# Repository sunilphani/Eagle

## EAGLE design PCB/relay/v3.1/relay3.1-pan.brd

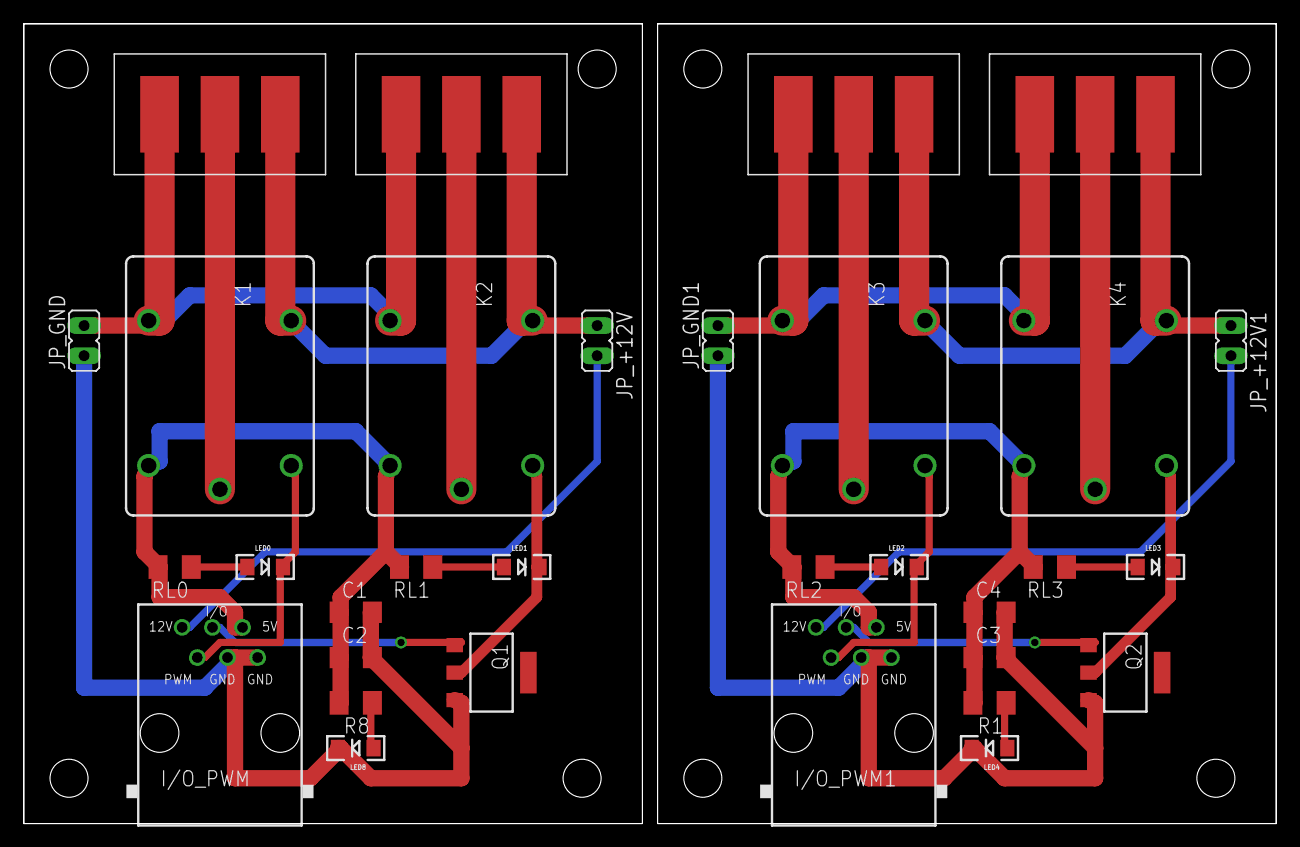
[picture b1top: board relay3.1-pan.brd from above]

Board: 2 copper layers, 105.4 x 67.3 mm, 32 parts (0 on the bottom side), 26 nets.

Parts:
C1, C4: 10uF; C1206
C2, C3: 100nF; C1206
I/O_PWM, I/O_PWM1: I2C 1; RJ12-STRAIGHT
JP_+12V, JP_+12V1: JP1
JP_GND, JP_GND1: JP1
K1, K2, K3, K4: JS-M1-9V-5; JS-M
LED0, LED1, LED2, LED3, LED4, LED8: LED-1206
Q1, Q2: BSP75; PG-SOT-223
R1, R8: 1K; M1206
RL0, RL1, RL2, RL3: 1K; M1206
X1, X2, X3, X4: 22-23-20315.08S; 3-PIN-5.08S

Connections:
+5V: C1.1, C2.1, I/O_PWM.+5V, K1.2, K2.2, R8.2, RL0.2, RL1.2
+5V1: C3.1, C4.1, I/O_PWM1.+5V, K3.2, K4.2, R1.2, RL2.2, RL3.2
+12V: I/O_PWM.+12V, JP_+12V.2
+12V1: I/O_PWM1.+12V, JP_+12V1.2
+12VRELAY: JP_+12V.1, K1.NO, K2.NO, X1.1, X2.1
+12VRELAY1: JP_+12V1.1, K3.NO, K4.NO, X3.1, X4.1
GND: C1.2, C2.2, I/O_PWM.GND1, I/O_PWM.GND2, JP_GND.1, LED8.C, Q1.3
GND1: C3.2, C4.2, I/O_PWM1.GND1, I/O_PWM1.GND2, JP_GND1.1, LED4.C, Q2.3
GNDRELAY: JP_GND.2, K1.NC, K2.NC, X1.3, X2.3
GNDRELAY1: JP_GND1.2, K3.NC, K4.NC, X3.3, X4.3
I/O: I/O_PWM.I/O, Q1.1
I/O1: I/O_PWM1.I/O, Q2.1
unnamed: K2.1, LED1.C, Q1.2
unnamed: LED0.A, RL0.1
unnamed: K4.1, LED3.C, Q2.2
unnamed: LED1.A, RL1.1
unnamed: K2.C, X1.2
unnamed: LED2.A, RL2.1
unnamed: LED3.A, RL3.1
unnamed: LED4.A, R1.1
unnamed: K4.C, X3.2
unnamed: LED8.A, R8.1
POWER1: K1.C, X2.2
POWER2: K3.C, X4.2
PWM: I/O_PWM.PWM, K1.1, LED0.C
PWM1: I/O_PWM1.PWM, K3.1, LED2.C

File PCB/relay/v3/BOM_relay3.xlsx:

Qty | Value | Device | Package | Parts | Description
2 |  | JP1Q | JP1 | JP_+12V
3 |  | LED1206 | LED-1206 | LED0
1 | 100nF | C-EUC1206 | C1206 | C2 | CAPACITOR
1 | 10uF | C-EUC1206 | C1206 | C1 | CAPACITOR
3 | 1K | R-EU_M1206 | M1206 | R8
2 | 22-23-20315.08S | 22-23-20315.08S | 3-PIN-5.08S | X1
1 | BSP75 | BSP613P | PG-SOT-223 | Q1 | SIPMOS (R) Small-Signal-Transistor P-Channel (2 Drain)
1 | I2C 1 | RJ12STRAIGHT | RJ12-STRAIGHT | I/O_PWM | CORCOM Modular RJ Jacks No Shield
2 | JS-M1-9V-5 | JS-M1-9V-5 | JS-M | K1

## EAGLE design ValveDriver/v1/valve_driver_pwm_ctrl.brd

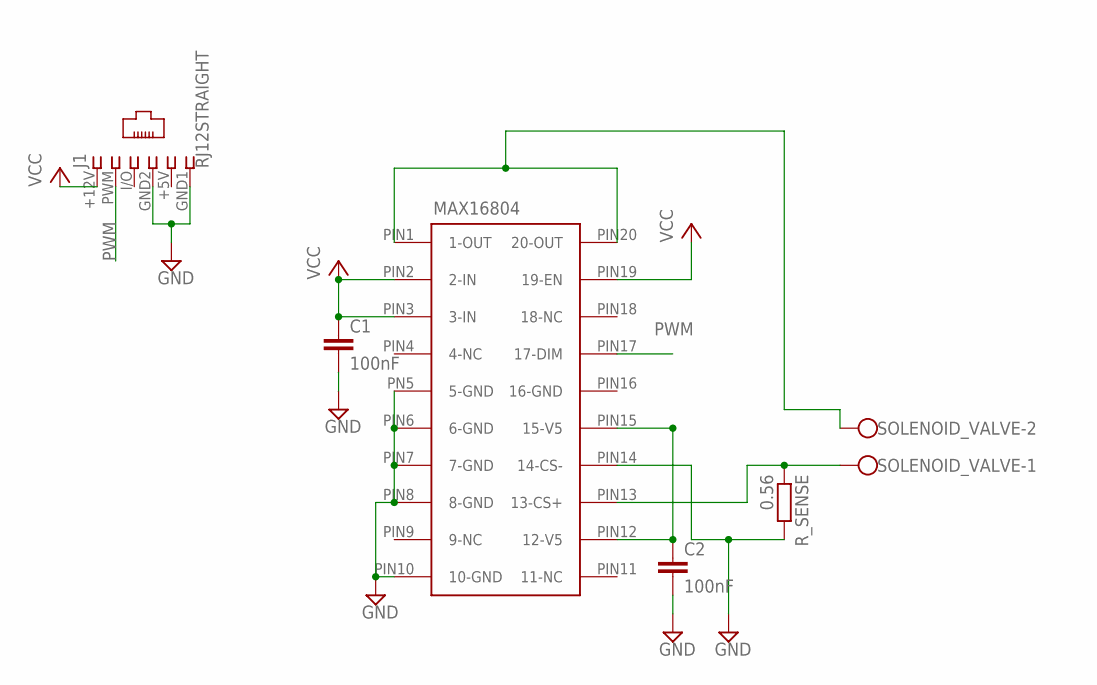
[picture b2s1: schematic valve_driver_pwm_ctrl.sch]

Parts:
C1, C2: 100nF; C1206
J1: RJ12STRAIGHT; RJ12-STRAIGHT
R_SENSE: 0.56; M1206
SOLENOID_VALVE: W237-102
U$1: MAX16804ATP+; TQFN-20

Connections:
GND: C1.2, C2.2, J1.GND1 (6), J1.GND2 (4), R_SENSE.2, U$1.PIN6 (6-GND), U$1.PIN7 (7-GND), U$1.PIN8 (8-GND), U$1.PIN10 (10-GND), U$1.PIN14 (14-CS-), U$1.PN5 (5-GND)
unnamed: SOLENOID_VALVE.2, U$1.PIN1 (1-OUT), U$1.PIN20 (20-OUT)
unnamed: C2.1, U$1.PIN12 (12-V5), U$1.PIN15 (15-V5)
unnamed: R_SENSE.1, SOLENOID_VALVE.1, U$1.PIN13 (13-CS+)
PWM: J1.PWM (2), U$1.PIN17 (17-DIM)
VCC: C1.1, J1.+12V (1), U$1.PIN2 (2-IN), U$1.PIN3 (3-IN), U$1.PIN19 (19-EN)

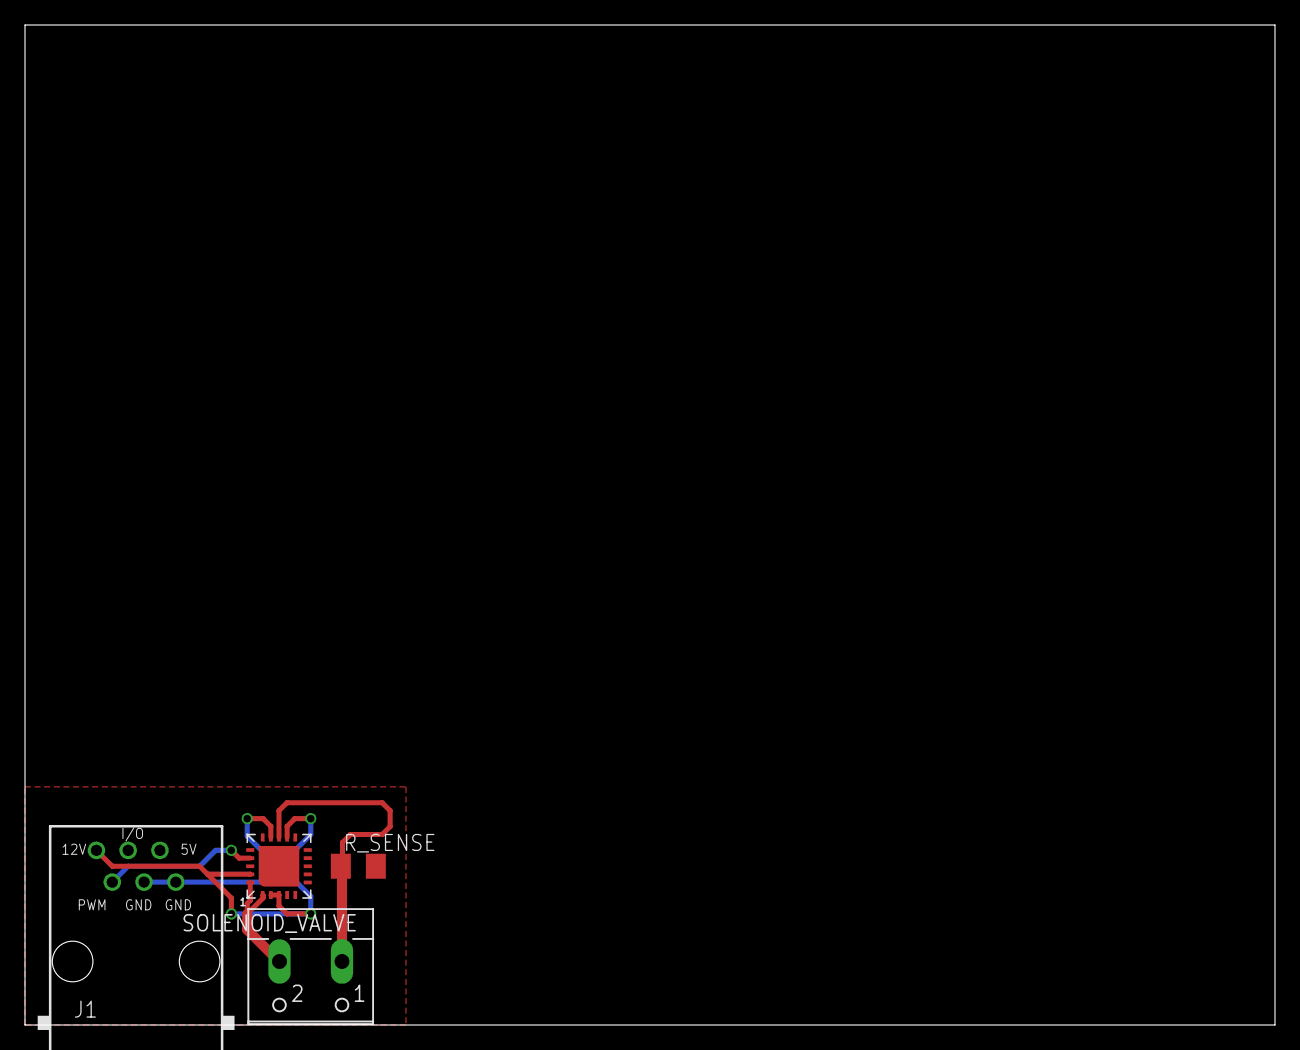
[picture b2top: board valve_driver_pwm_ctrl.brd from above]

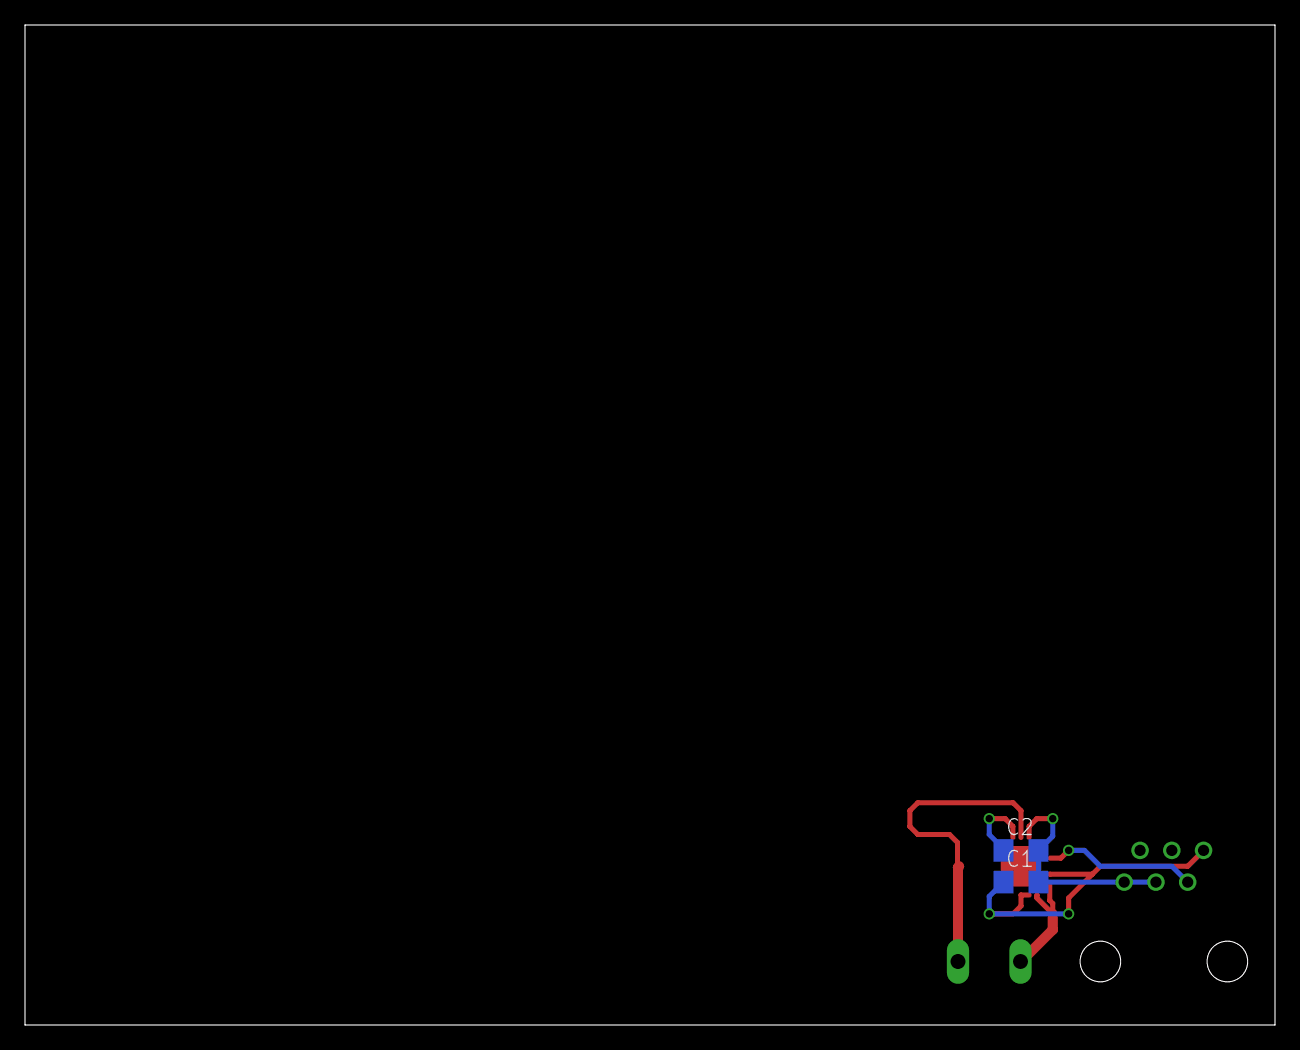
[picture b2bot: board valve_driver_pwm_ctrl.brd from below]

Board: 2 copper layers, 100.0 x 80.0 mm, 6 parts (2 on the bottom side), 6 nets.

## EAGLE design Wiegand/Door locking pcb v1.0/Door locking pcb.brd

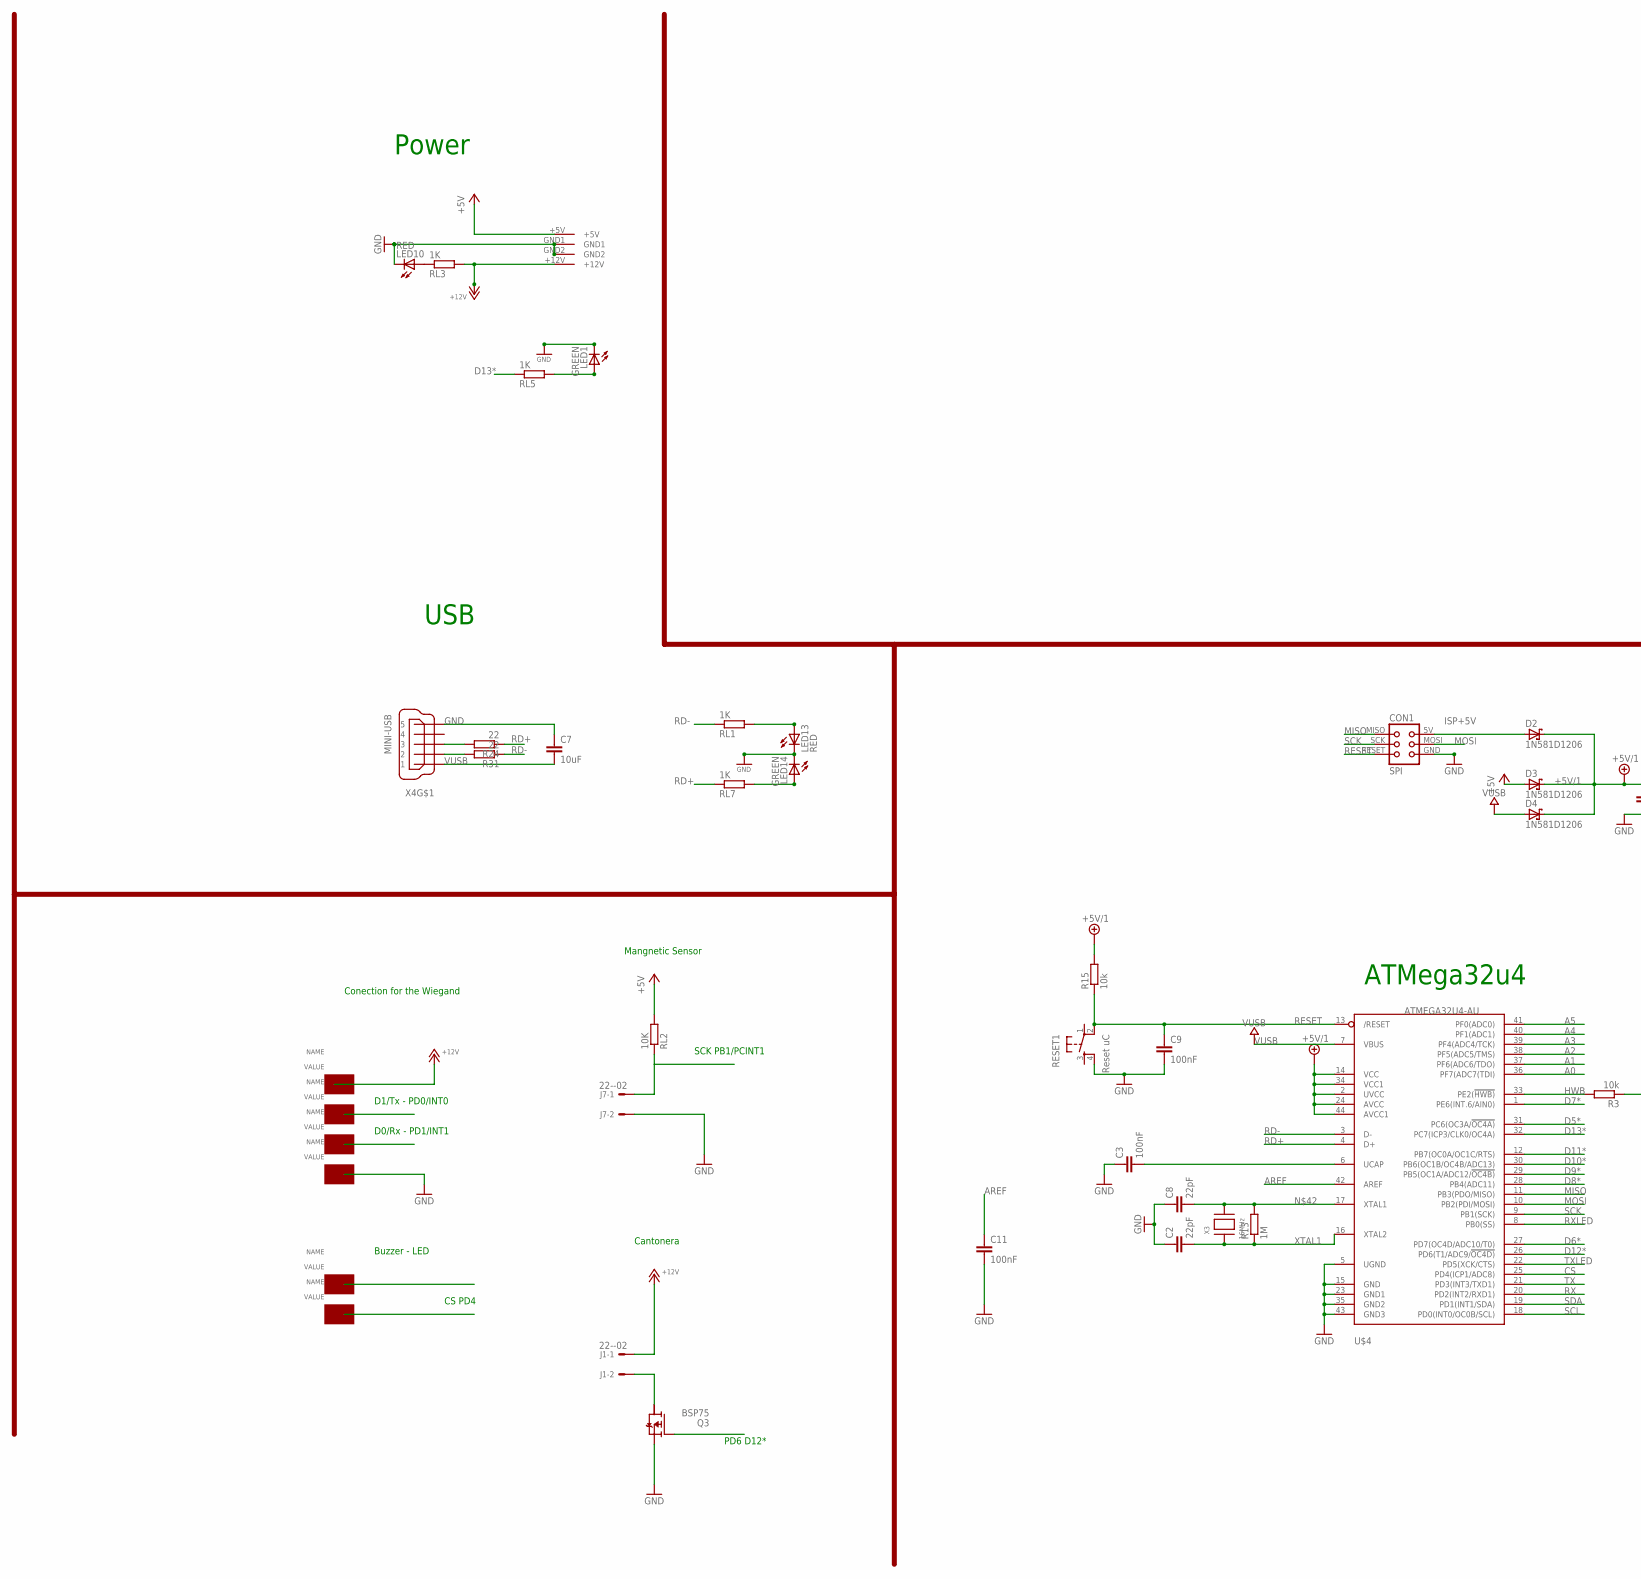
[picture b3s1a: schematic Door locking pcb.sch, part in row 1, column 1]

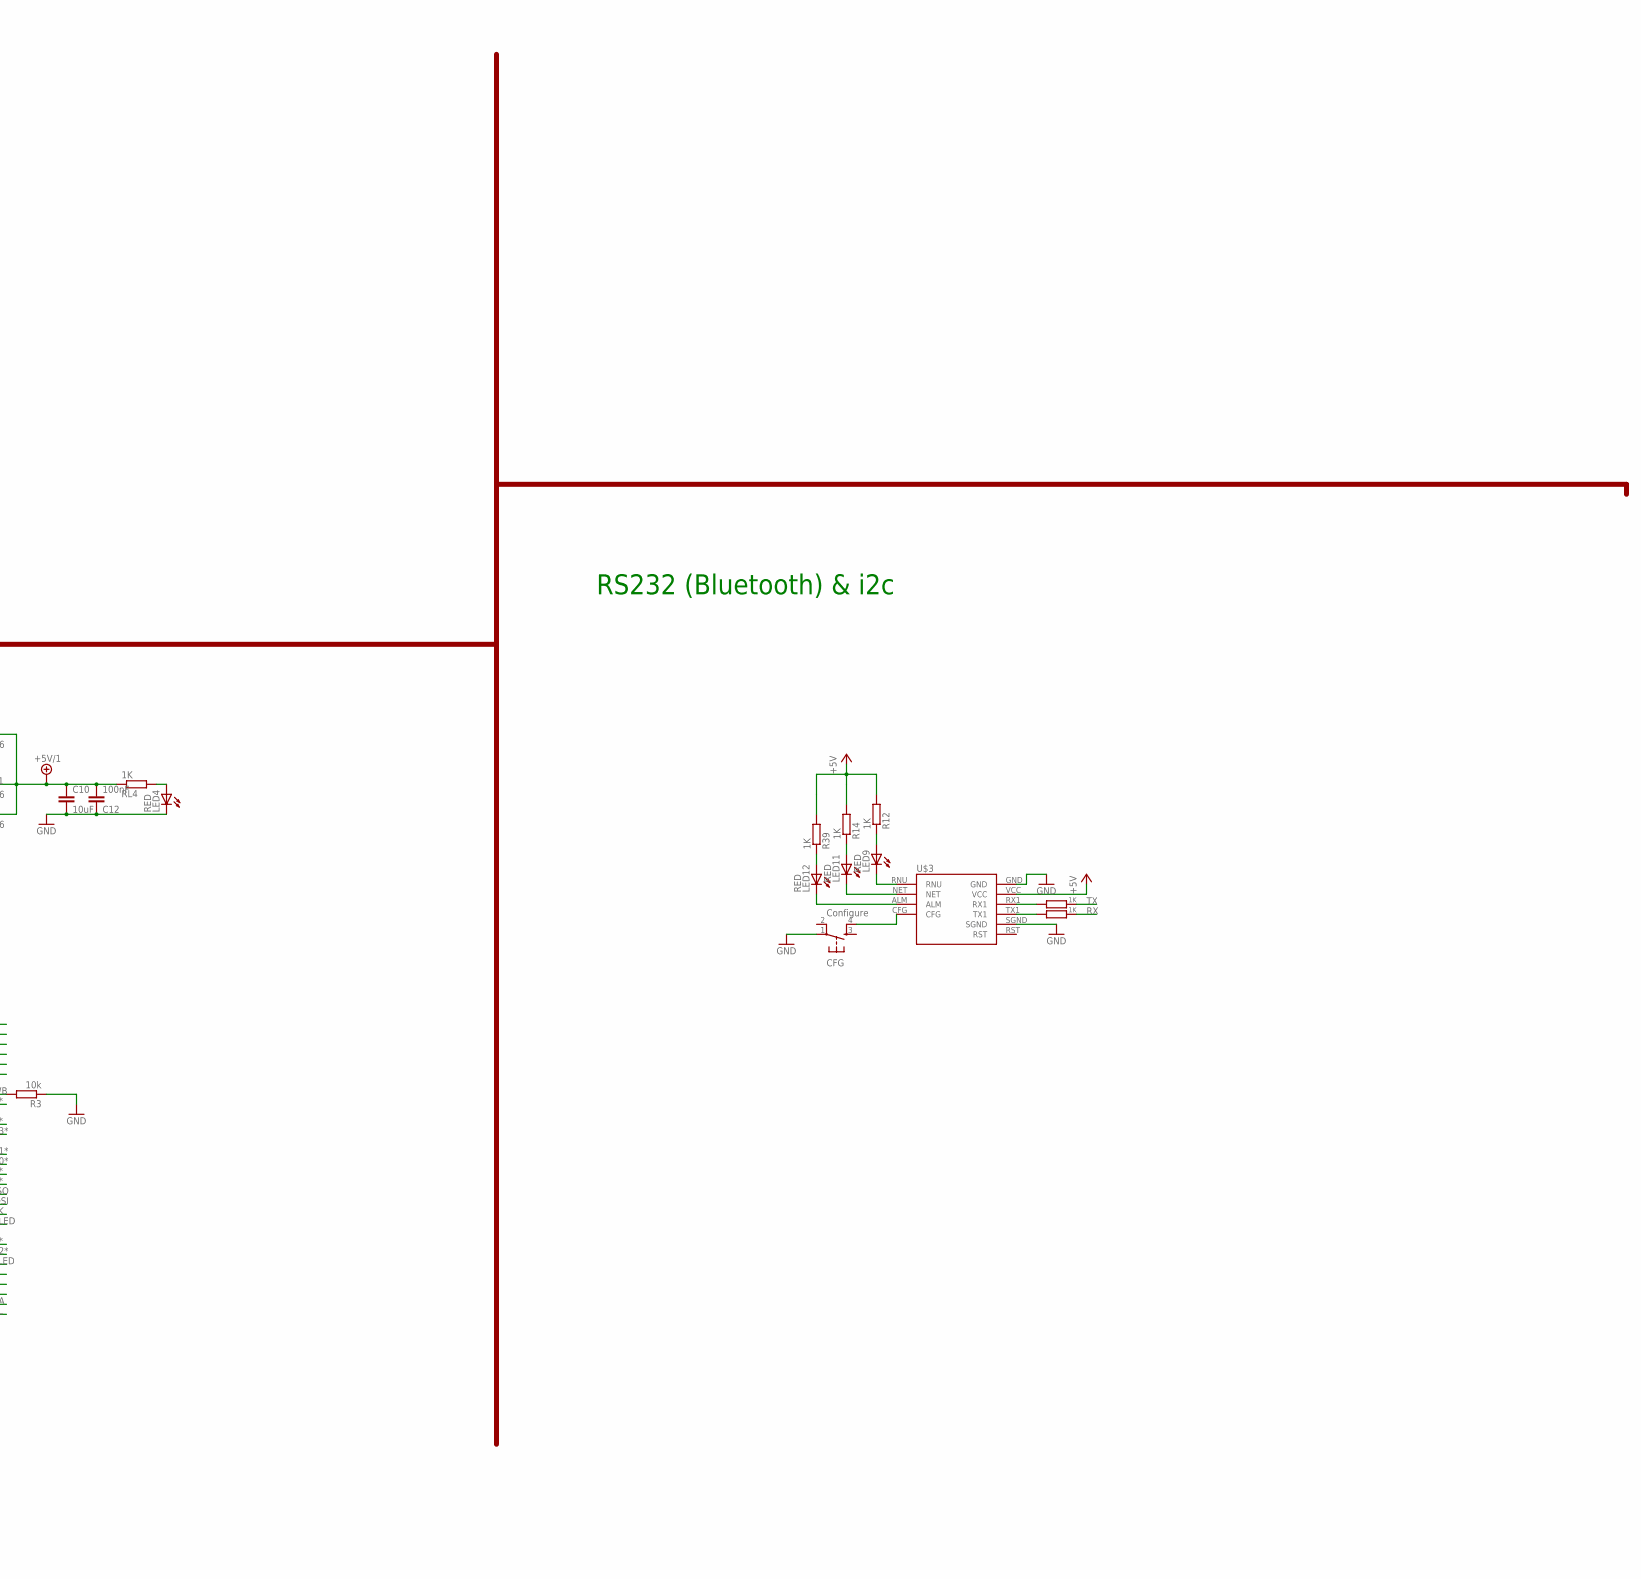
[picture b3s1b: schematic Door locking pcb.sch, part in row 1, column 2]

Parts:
C2, C8: 22pF; C1206
C3, C9, C11, C12: 100nF; C1206
C7, C10: 10uF; C1206
CFG: Configure; TACTILE_SWITCH_SMD
CON1: SPI; TC2030-MCP-NL
D2, D3, D4: 1N581D1206; LED-1206
J1, J7: 22--02; 2-PIN-5.08S
LED1, LED14: GREEN; CHIPLED_1206
LED4, LED9, LED10, LED11, LED12, LED13: RED; CHIPLED_1206
PIN1, PIN2, PIN3, PIN4, PIN5, PIN6: TERMINALSUPERFICIAL; ELPUTAS
Q3: BSP75; PG-SOT-223
R3, R15: 10k; M0805
R8, R11, R12, R14, R39: 1K; R0805
R13: 1M; R1206
R24, R31: 22; M1206
RESET1: Reset uC; TACTILE_SWITCH_SMD
RL1, RL3, RL4, RL5, RL7: 1K; R0805
RL2: 10K; R0805
U$3: SZ05-ZIGBEE
U$4: ATMEGA32U4-AU; TQFP44
U$6: KPJX-4S-S
X3: 16MHz; NX6035
X4: MINI-USB; 32005-201

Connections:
+5V: D3.A, R12.2, R14.2, R39.2, RL2.2, U$3.VCC, U$6.+5V
+5V/1: C10.1, C12.2, D2.C, D3.C, D4.C, R15.2, RL4.1, U$4.2 (UVCC), U$4.14 (VCC), U$4.24 (AVCC), U$4.34 (VCC1), U$4.44 (AVCC1)
+12V: J1.1, PIN6.P$4 (2), RL3.2, U$6.+12V
A0: U$4.36 (PF7(ADC7(TDI))
A1: U$4.37 (PF6(ADC6/TDO))
A2: U$4.38 (PF5(ADC5/TMS))
A3: U$4.39 (PF4(ADC4/TCK))
A4: U$4.40 (PF1(ADC1))
A5: U$4.41 (PF0(ADC0))
AREF: C11.1, U$4.42 (AREF)
D5*: U$4.31 (PC6(OC3A/!OC4A))
D6*: U$4.27 (PD7(OC4D/ADC10/T0))
D7*: U$4.1 (PE6(INT.6/AIN0))
D8*: U$4.28 (PB4(ADC11))
D9*: U$4.29 (PB5(OC1A/ADC12/!OC4B))
D10*: U$4.30 (PB6(OC1B/OC4B/ADC13))
D11*: U$4.12 (PB7(OC0A/OC1C/RTS))
D12*: Q3.1 (G), U$4.26 (PD6(T1/ADC9/!OC4D))
D13*: RL5.1, U$4.32 (PC7(ICP3/CLK0/OC4A))
D+USB: R24.2, X4.3
D-USB: R31.2, X4.2
GND: C2.1, C3.1, C7.1, C8.1, C9.2, C10.2, C11.2, C12.1, CFG.1, CON1.GND, J7.2, LED1.C, LED4.C, LED10.C, LED13.C, LED14.C, PIN5.P$3 (1), Q3.3 (S), R3.1, RESET1.4, U$3.GND, U$3.SGND, U$4.5 (UGND), U$4.15 (GND), U$4.23 (GND1), U$4.35 (GND2), U$4.43 (GND3), U$6.GND1, U$6.GND2, X4.5; also elsewhere on the board
GND1: LED9.C, U$3.RNU
GND2: LED11.C, U$3.NET
GND3: LED12.C, U$3.ALM
HWB: R3.2, U$4.33 (PE2(!HWB))
ISP+5V: CON1.5V (VCC), D2.A
MISO: CON1.MISO, U$4.11 (PB3(PDO/MISO))
MOSI: CON1.MOSI, U$4.10 (PB2(PDI/MOSI))
unnamed: J1.2, Q3.2 (D)
unnamed: LED1.A, RL5.2
unnamed: R11.2, U$3.RX1
unnamed: LED4.A, RL4.2
unnamed: C3.2, U$4.6 (UCAP)
unnamed: R8.2, U$3.TX1
unnamed: LED9.A, R12.1
unnamed: LED11.A, R14.1
unnamed: LED12.A, R39.1
unnamed: CFG.4, U$3.CFG
unnamed: C8.2, R13.2, U$4.17 (XTAL1), X3.P$2
unnamed: LED10.A, RL3.1
unnamed: LED13.A, RL1.2
unnamed: LED14.A, RL7.2
RD+: R24.1, RL7.1, U$4.4 (D+)
RD-: R31.1, RL1.1, U$4.3 (D-)
RESET: C9.1, CON1.RESET, R15.1, RESET1.2, U$4.13 (/RESET)
RX: R8.1, U$4.20 (PD2(INT2/RXD1))
RXLED: U$4.8 (PB0(SS))
SCK: CON1.SCK, J7.1, RL2.1, U$4.9 (PB1(SCK))
SCL: PIN1.P$3 (1), U$4.18 (PD0(INT0/OC0B/SCL))
SDA: PIN2.P$3 (1), U$4.19 (PD1(INT1/SDA))
TX: R11.1, U$4.21 (PD3(INT3/TXD1))
TXLED: U$4.22 (PD5(XCK/CTS))
VUSB: C7.2, D4.A, U$4.7 (VBUS), X4.1
XTAL1: C2.2, R13.1, U$4.16 (XTAL2), X3.P$1

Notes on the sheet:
ATMega32u4
USB
Power
RS232 (Bluetooth) & i2c
Conection for the Wiegand
Cantonera
Mangnetic Sensor
Buzzer - LED
D1/Tx - PD0/INT0
D0/Rx - PD1/INT1
SCK PB1/PCINT1
CS PD4
PD6 D12*

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
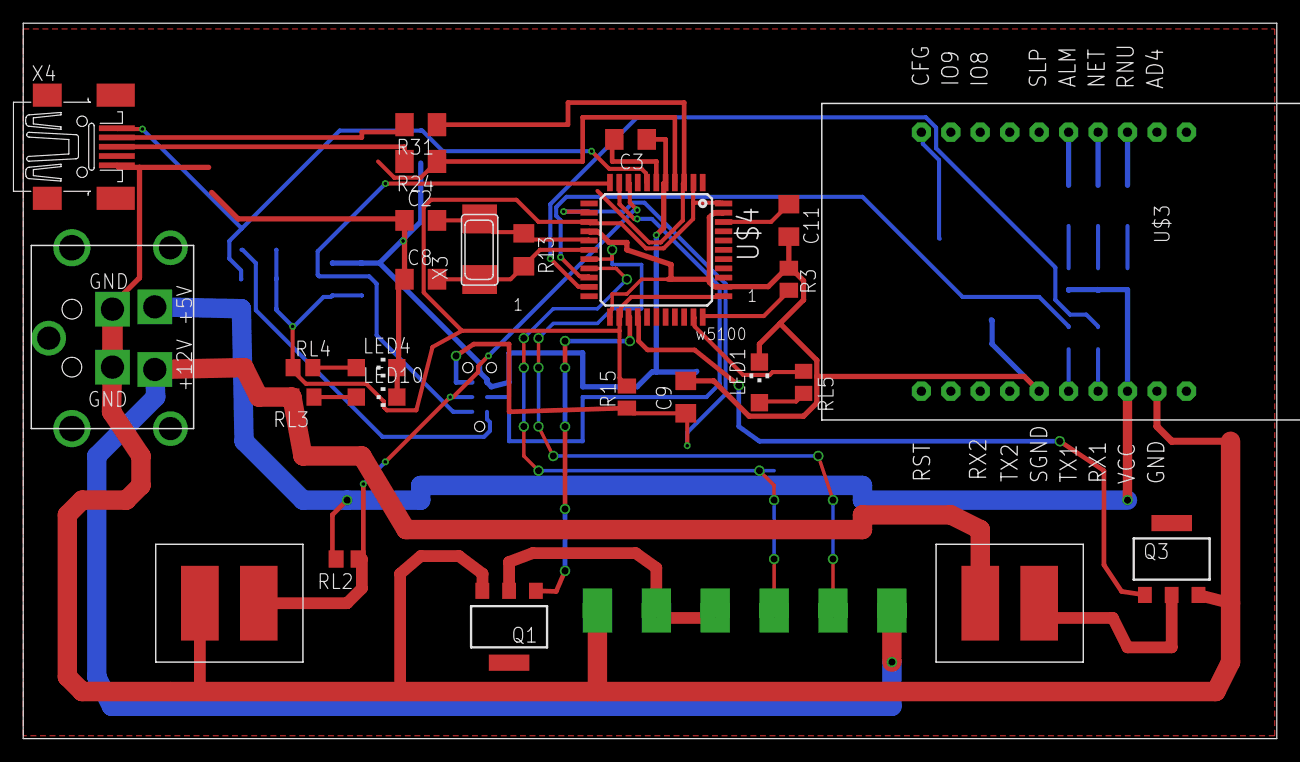
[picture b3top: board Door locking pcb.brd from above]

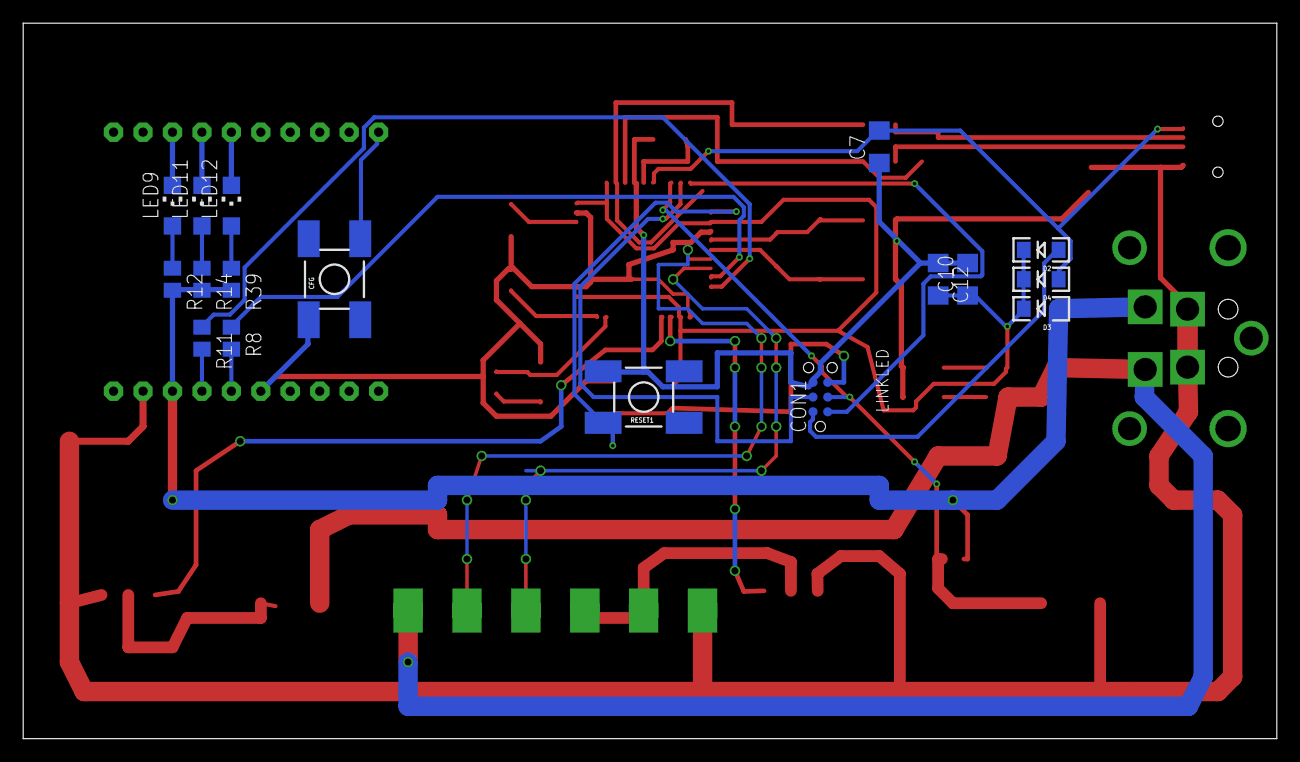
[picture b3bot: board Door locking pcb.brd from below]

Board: 2 copper layers, 108.1 x 61.7 mm, 49 parts (17 on the bottom side), 40 nets.

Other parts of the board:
Q1: BSP75; PG-SOT-223

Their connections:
GND: Q1.3; also elsewhere on the board

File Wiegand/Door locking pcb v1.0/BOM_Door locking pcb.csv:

"Qty";"Value";"Device";"Package";"Parts";"Description";"";
"4";"100nF";"C-EUC1206";"C1206";"C3, C9, C11, C12";"CAPACITOR, European symbol";"";
"1";"10K";"R-EU_R0805";"R0805";"RL2";"RESISTOR, European symbol";"";
"2";"10k";"R-EU_M0805";"M0805";"R3, R15";"RESISTOR, European symbol";"";
"2";"10uF";"C-EUC1206";"C1206";"C7, C10";"CAPACITOR, European symbol";"";
"1";"16MHz";"XTALNX6035";"NX6035";"X3";"Low cost SMT crystals, no capacitors included";"";
"8";"1K";"R-EU_R0805";"R0805";"R8, R11, R12, R14, R39, RL3, RL4, RL5";"RESISTOR, European symbol";"";
"1";"1M";"R-EU_R1206";"R1206";"R13";"RESISTOR, European symbol";"";
"3";"1N581D1206";"1N581D1206";"LED-1206";"D2, D3, D4";"1.0A SCHOTTKY BARRIER RECTIFIER";"";
"2";"22";"R-EU_M1206";"M1206";"R24, R31";"RESISTOR, European symbol";"";
"2";"22--02";"22--02";"2-PIN-5.08S";"J1, J7";"CONNECTOR";"";
"2";"22pF";"C-EUC1206";"C1206";"C2, C8";"CAPACITOR, European symbol";"";
"1";"ATMEGA32U4-AU";"ATMEGA32U4-AU";"TQFP44";"U$4";"http://www.ladyada.net/library/eagle";"";
"2";"BSP75";"BSP613P";"PG-SOT-223";"Q1, Q3";"SIPMOS (R) Small-Signal-Transistor P-Channel (2 Drain)";"";
"1";"Configure";"TAC_SWITCHSMD";"TACTILE_SWITCH_SMD";"CFG";"Momentary Switch";"";
"1";"GREEN";"LEDCHIPLED_1206";"CHIPLED_1206";"LED1";"LED";"";
"1";"KPJX-4S-S";"KPJX-4S-S";"KPJX-4S-S";"U$6";"";"";
"1";"MINI-USB";"MINI-USB-SCHIELD-32005-201";"32005-201";"X4";"MINI USB-B Conector";"";
"5";"RED";"LEDCHIPLED_1206";"CHIPLED_1206";"LED4, LED9, LED10, LED11, LED12";"LED";"";
"1";"Reset uC";"TAC_SWITCHSMD";"TACTILE_SWITCH_SMD";"RESET1";"Momentary Switch";"";
"1";"SPI";"TINYISPT";"TC2030-MCP-NL";"CON1";"CONNECTOR";"";
"1";"SZ05-ZIGBEE";"SZ05-ZIGBEE";"SZ05-ZIGBEE";"U$3";"";"";
"6";"TERMINALSUPERFICIAL";"TERMINALSUPERFICIAL";"ELPUTAS";"PIN1, PIN2, PIN3, PIN4, PIN5, PIN6";"";"";

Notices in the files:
parts and their libraries:
SparkFun: Licensing: CC v3.0 Share-Alike You are welcome to use this library for commercial purposes.
lpatiny: ©2009 ROFA.cz - modified and updated by Robert Darlington ‹rdarlington@gmail.com›
